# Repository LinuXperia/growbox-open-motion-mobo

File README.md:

# growbox-open-motion-mobo
A general purpose open source Arduino DUE based motion controller designed to run the Synthetos G2 motion control fimware 

Created and designed by Adam Vadala-Roth

https://hackaday.io/adamjvr

https://github.com/adamjvr

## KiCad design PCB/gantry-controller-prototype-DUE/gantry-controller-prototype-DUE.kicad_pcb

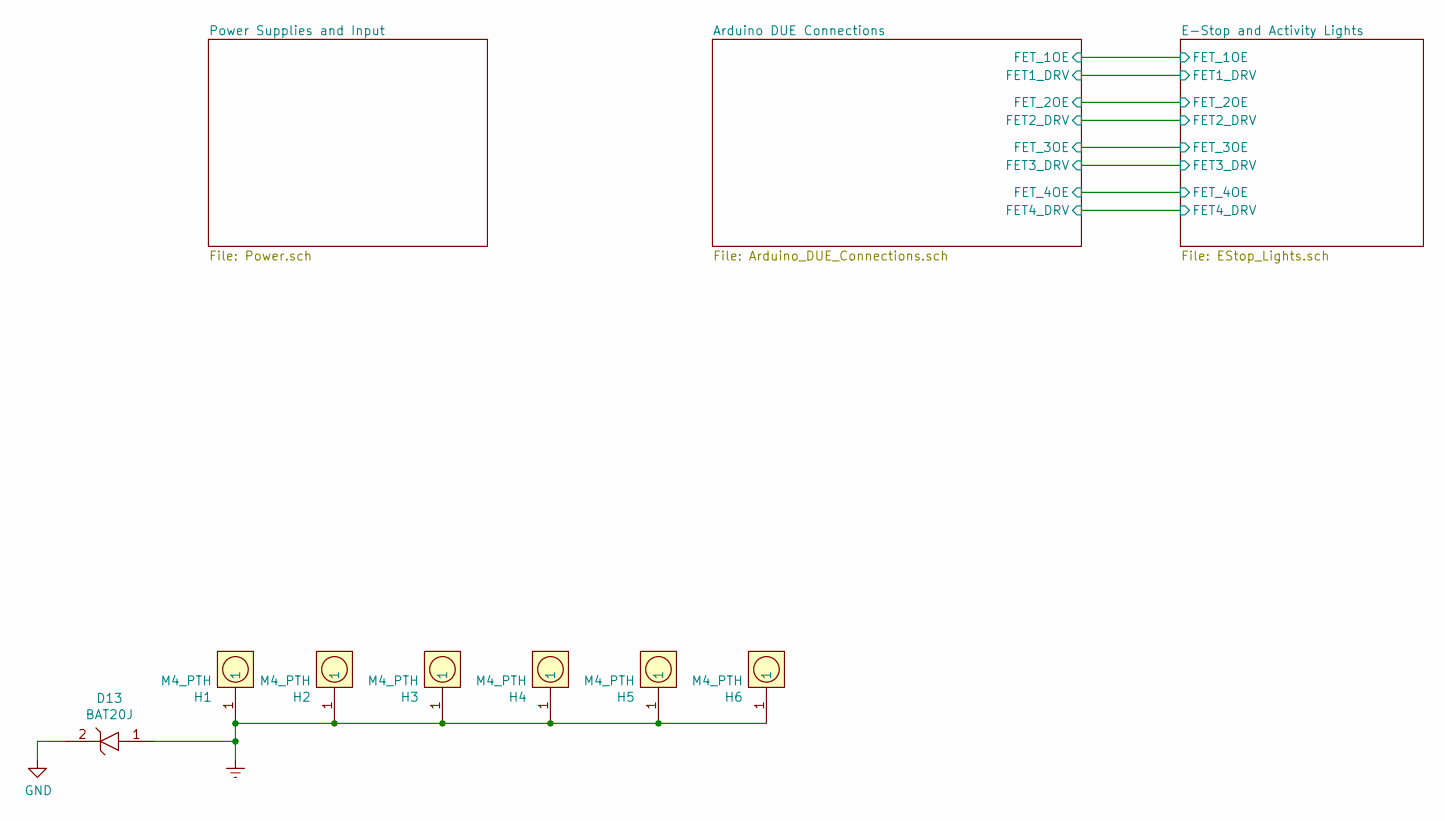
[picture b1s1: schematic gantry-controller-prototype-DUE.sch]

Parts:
D13: BAT20JFILM; Tolerance *; Voltage 23V; MFR# BAT20JFILM
H1, H2, H3, H4, H5, H6: M4_PTH; M4_HOLE; Tolerance *; Voltage *; MFR# *

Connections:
Earth: D13.1, H1.1, H2.1, H3.1, H4.1, H5.1, H6.1
GND: D13.2; also elsewhere on the board

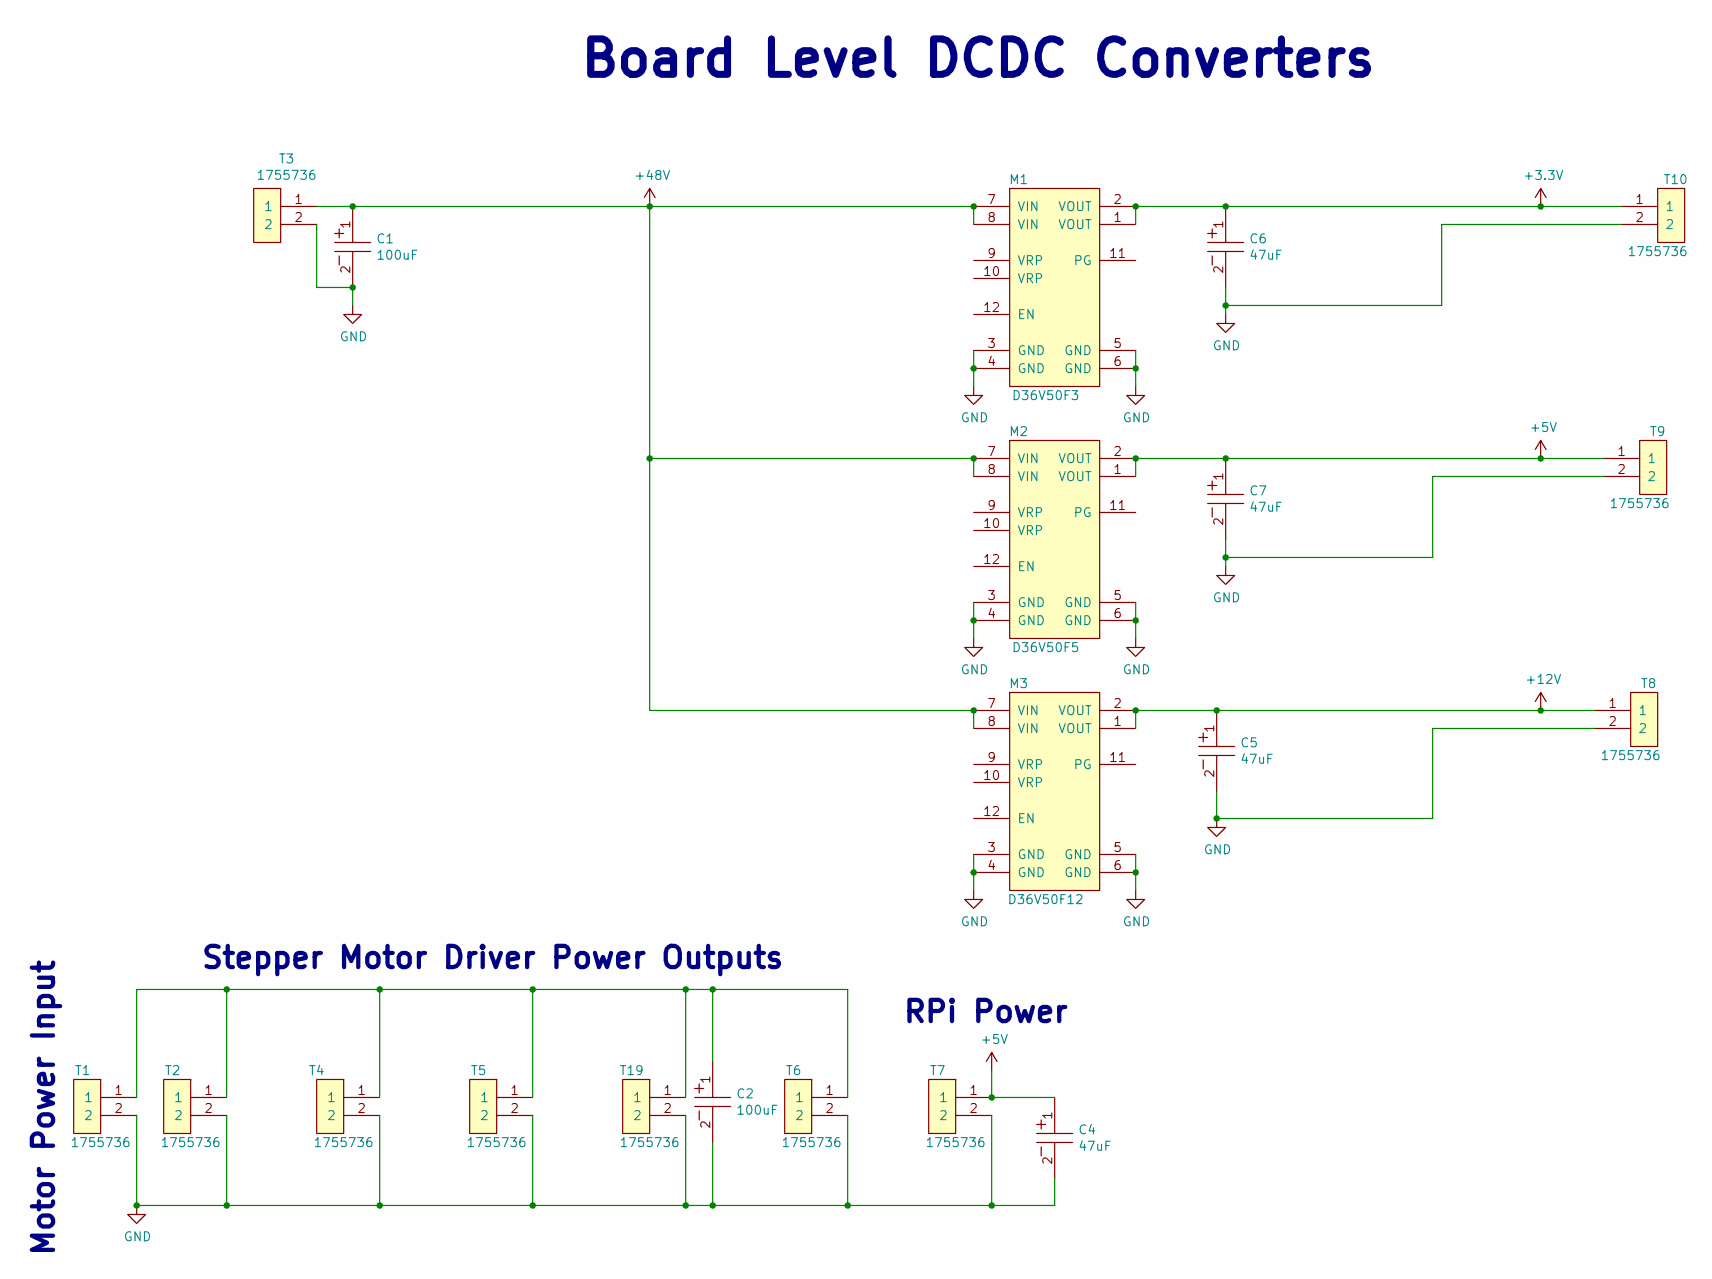
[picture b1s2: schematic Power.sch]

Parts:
C1, C2: UUX1J101MNL1GS; Tolerance 20%; Voltage 63V; MFR# UUX1J101MNL1GS
C4, C5, C6, C7: UWT1H470MCL1GS; Tolerance 20%; Voltage 63V; MFR# UWT1H470MCL1GS
M1: D36V50F3; D36V50Fx; Tolerance *; Voltage 50V In 3.3V OUT; MFR# D36V50F3
M2: D36V50F5; D36V50Fx; Tolerance *; Voltage 50V In 5V OUT; MFR# D36V50F5
M3: D36V50F12; D36V50Fx; Tolerance *; Voltage 50V In 12V OUT; MFR# D36V50F12
T1, T2, T3, T4, T5, T6, T7, T8, T9, T10, T19: 1755736; PhoenixContact_MSTBVA-G_02x5.08mm_Vertical; Tolerance *; Voltage 300V; MFR# 1755736

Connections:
+3V3: C6.1, M1.1 (VOUT), M1.2 (VOUT), T10.1; also elsewhere on the board
+5V: C4.1, C7.1, M2.1 (VOUT), M2.2 (VOUT), T7.1, T9.1; also elsewhere on the board
+12V: C5.1, M3.1 (VOUT), M3.2 (VOUT), T8.1; also elsewhere on the board
+48V: C1.1, M1.7 (VIN), M1.8 (VIN), M2.7 (VIN), M2.8 (VIN), M3.7 (VIN), M3.8 (VIN), T3.1
GND: C1.2, C2.2, C4.2, C5.2, C6.2, C7.2, M1.3 (GND), M1.4 (GND), M1.5 (GND), M1.6 (GND), M2.3 (GND), M2.4 (GND), M2.5 (GND), M2.6 (GND), M3.3 (GND), M3.4 (GND), M3.5 (GND), M3.6 (GND), T1.2, T2.2, T3.2, T4.2, T5.2, T6.2, T7.2, T8.2, T9.2, T10.2, T19.2; also elsewhere on the board
unnamed: C2.1, T1.1, T2.1, T4.1, T5.1, T6.1, T19.1

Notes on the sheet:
Board Level DCDC Converters
Stepper Motor Driver Power Outputs
RPi Power
Motor Power Input

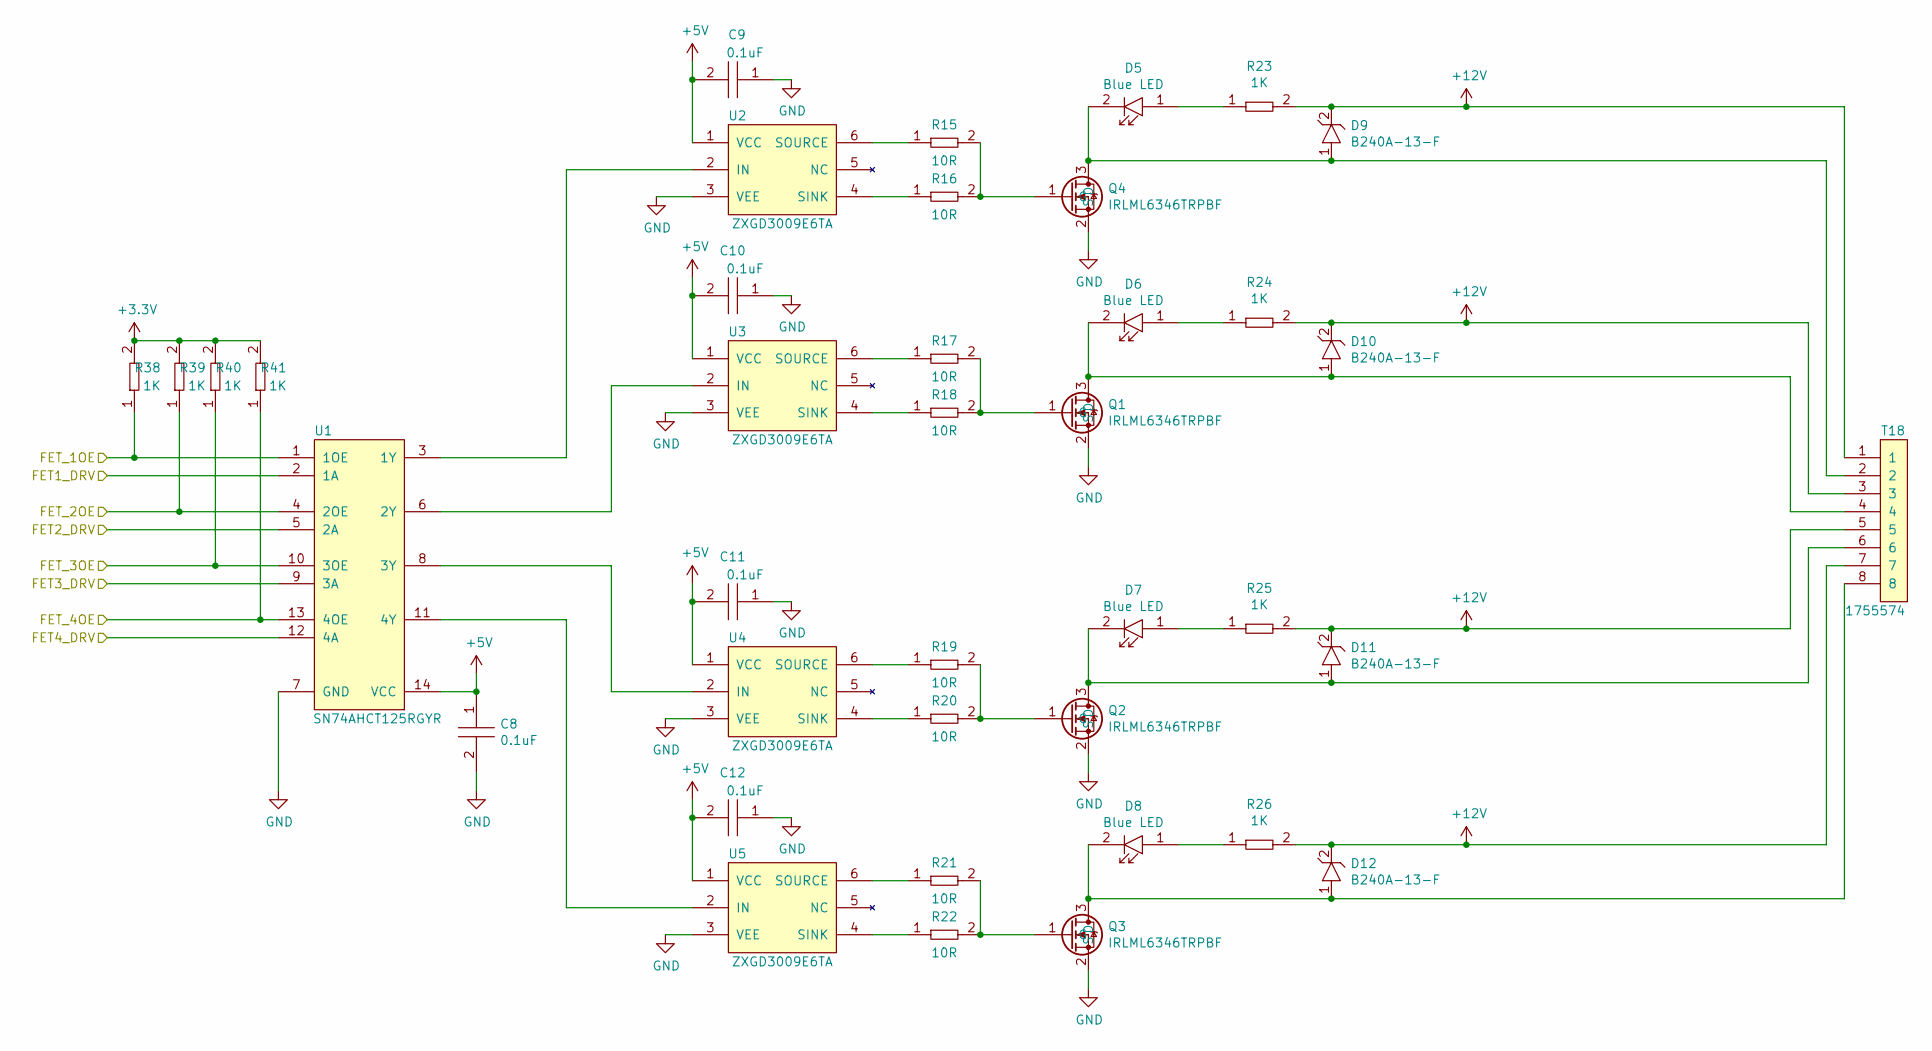
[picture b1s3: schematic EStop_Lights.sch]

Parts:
C8, C9, C10, C11, C12: GRM155R71E104KE14J; C0402; Tolerance 10%; Voltage 25V; MFR# GRM155R71E104KE14J
D5, D6, D7, D8: LTST-C194TBKT; LED0603; Tolerance *; Voltage 3.3V; MFR# LTST-C194TBKT
D9, D10, D11, D12: B240A-13-F; Tolerance *; Voltage 40V; MFR# B240A-13-F
Q1, Q2, Q3, Q4: IRLML6346TRPBF; SOT-23; Tolerance *; Voltage 30V; MFR# IRLML6346TRPBF
R15, R16, R17, R18, R19, R20, R21, R22: RC0402FR-0710RL; R0402; Tolerance 1%; Voltage *; MFR# RC0402FR-0710RL
R23, R24, R25, R26, R38, R39, R40, R41: RC0402FR-071KL; R0402; Tolerance 1%; Voltage *; MFR# RC0402FR-071KL
T18: 1755574; PhoenixContact_MSTBVA-G_08x5.00mm_Vertical; Tolerance *; Voltage 300V; MFR# 1755574
U1: SN74AHCT125RGYR; Tolerance *; Voltage 5V; MFR# SN74AHCT125RGYR
U2, U3, U4, U5: ZXGD3009E6TA; SOT-23-6_Handsoldering; Tolerance *; Voltage 40V; MFR# ZXGD3009E6TA

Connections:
+3V3: R38.2, R39.2, R40.2, R41.2; also elsewhere on the board
+5V: C8.1, C9.2, C10.2, C11.2, C12.2, U1.14 (VCC), U2.1 (VCC), U3.1 (VCC), U4.1 (VCC), U5.1 (VCC); also elsewhere on the board
+12V: D9.2, D10.2, D11.2, D12.2, R23.2, R24.2, R25.2, R26.2, T18.1, T18.3, T18.5, T18.7; also elsewhere on the board
/Arduino DUE Connections/FET1_DRV: U1.2 (1A); also elsewhere on the board
/Arduino DUE Connections/FET2_DRV: U1.5 (2A); also elsewhere on the board
/Arduino DUE Connections/FET3_DRV: U1.9 (3A); also elsewhere on the board
/Arduino DUE Connections/FET4_DRV: U1.12 (4A); also elsewhere on the board
/Arduino DUE Connections/FET_1OE: R38.1, U1.1 (1OE); also elsewhere on the board
/Arduino DUE Connections/FET_2OE: R39.1, U1.4 (2OE); also elsewhere on the board
/Arduino DUE Connections/FET_3OE: R40.1, U1.10 (3OE); also elsewhere on the board
/Arduino DUE Connections/FET_4OE: R41.1, U1.13 (4OE); also elsewhere on the board
GND: C8.2, C9.1, C10.1, C11.1, C12.1, Q1.2 (S), Q2.2 (S), Q3.2 (S), Q4.2 (S), U1.7 (GND), U2.3 (VEE), U3.3 (VEE), U4.3 (VEE), U5.3 (VEE); also elsewhere on the board
unnamed: D5.1, R23.1
unnamed: D5.2, D9.1, Q4.3 (D), T18.2
unnamed: D6.1, R24.1
unnamed: D7.1, R25.1
unnamed: D8.1, R26.1
unnamed: D6.2, D10.1, Q1.3 (D), T18.4
unnamed: D7.2, D11.1, Q2.3 (D), T18.6
unnamed: D8.2, D12.1, Q3.3 (D), T18.8
unnamed: Q1.1 (G), R17.2, R18.2
unnamed: Q2.1 (G), R19.2, R20.2
unnamed: Q3.1 (G), R21.2, R22.2
unnamed: Q4.1 (G), R15.2, R16.2
unnamed: R15.1, U2.6 (SOURCE)
unnamed: R16.1, U2.4 (SINK)
unnamed: R17.1, U3.6 (SOURCE)
unnamed: R18.1, U3.4 (SINK)
unnamed: R19.1, U4.6 (SOURCE)
unnamed: R20.1, U4.4 (SINK)
unnamed: R21.1, U5.6 (SOURCE)
unnamed: R22.1, U5.4 (SINK)
unnamed: U1.3 (1Y), U2.2 (IN)
unnamed: U1.6 (2Y), U3.2 (IN)
unnamed: U1.8 (3Y), U4.2 (IN)
unnamed: U1.11 (4Y), U5.2 (IN)

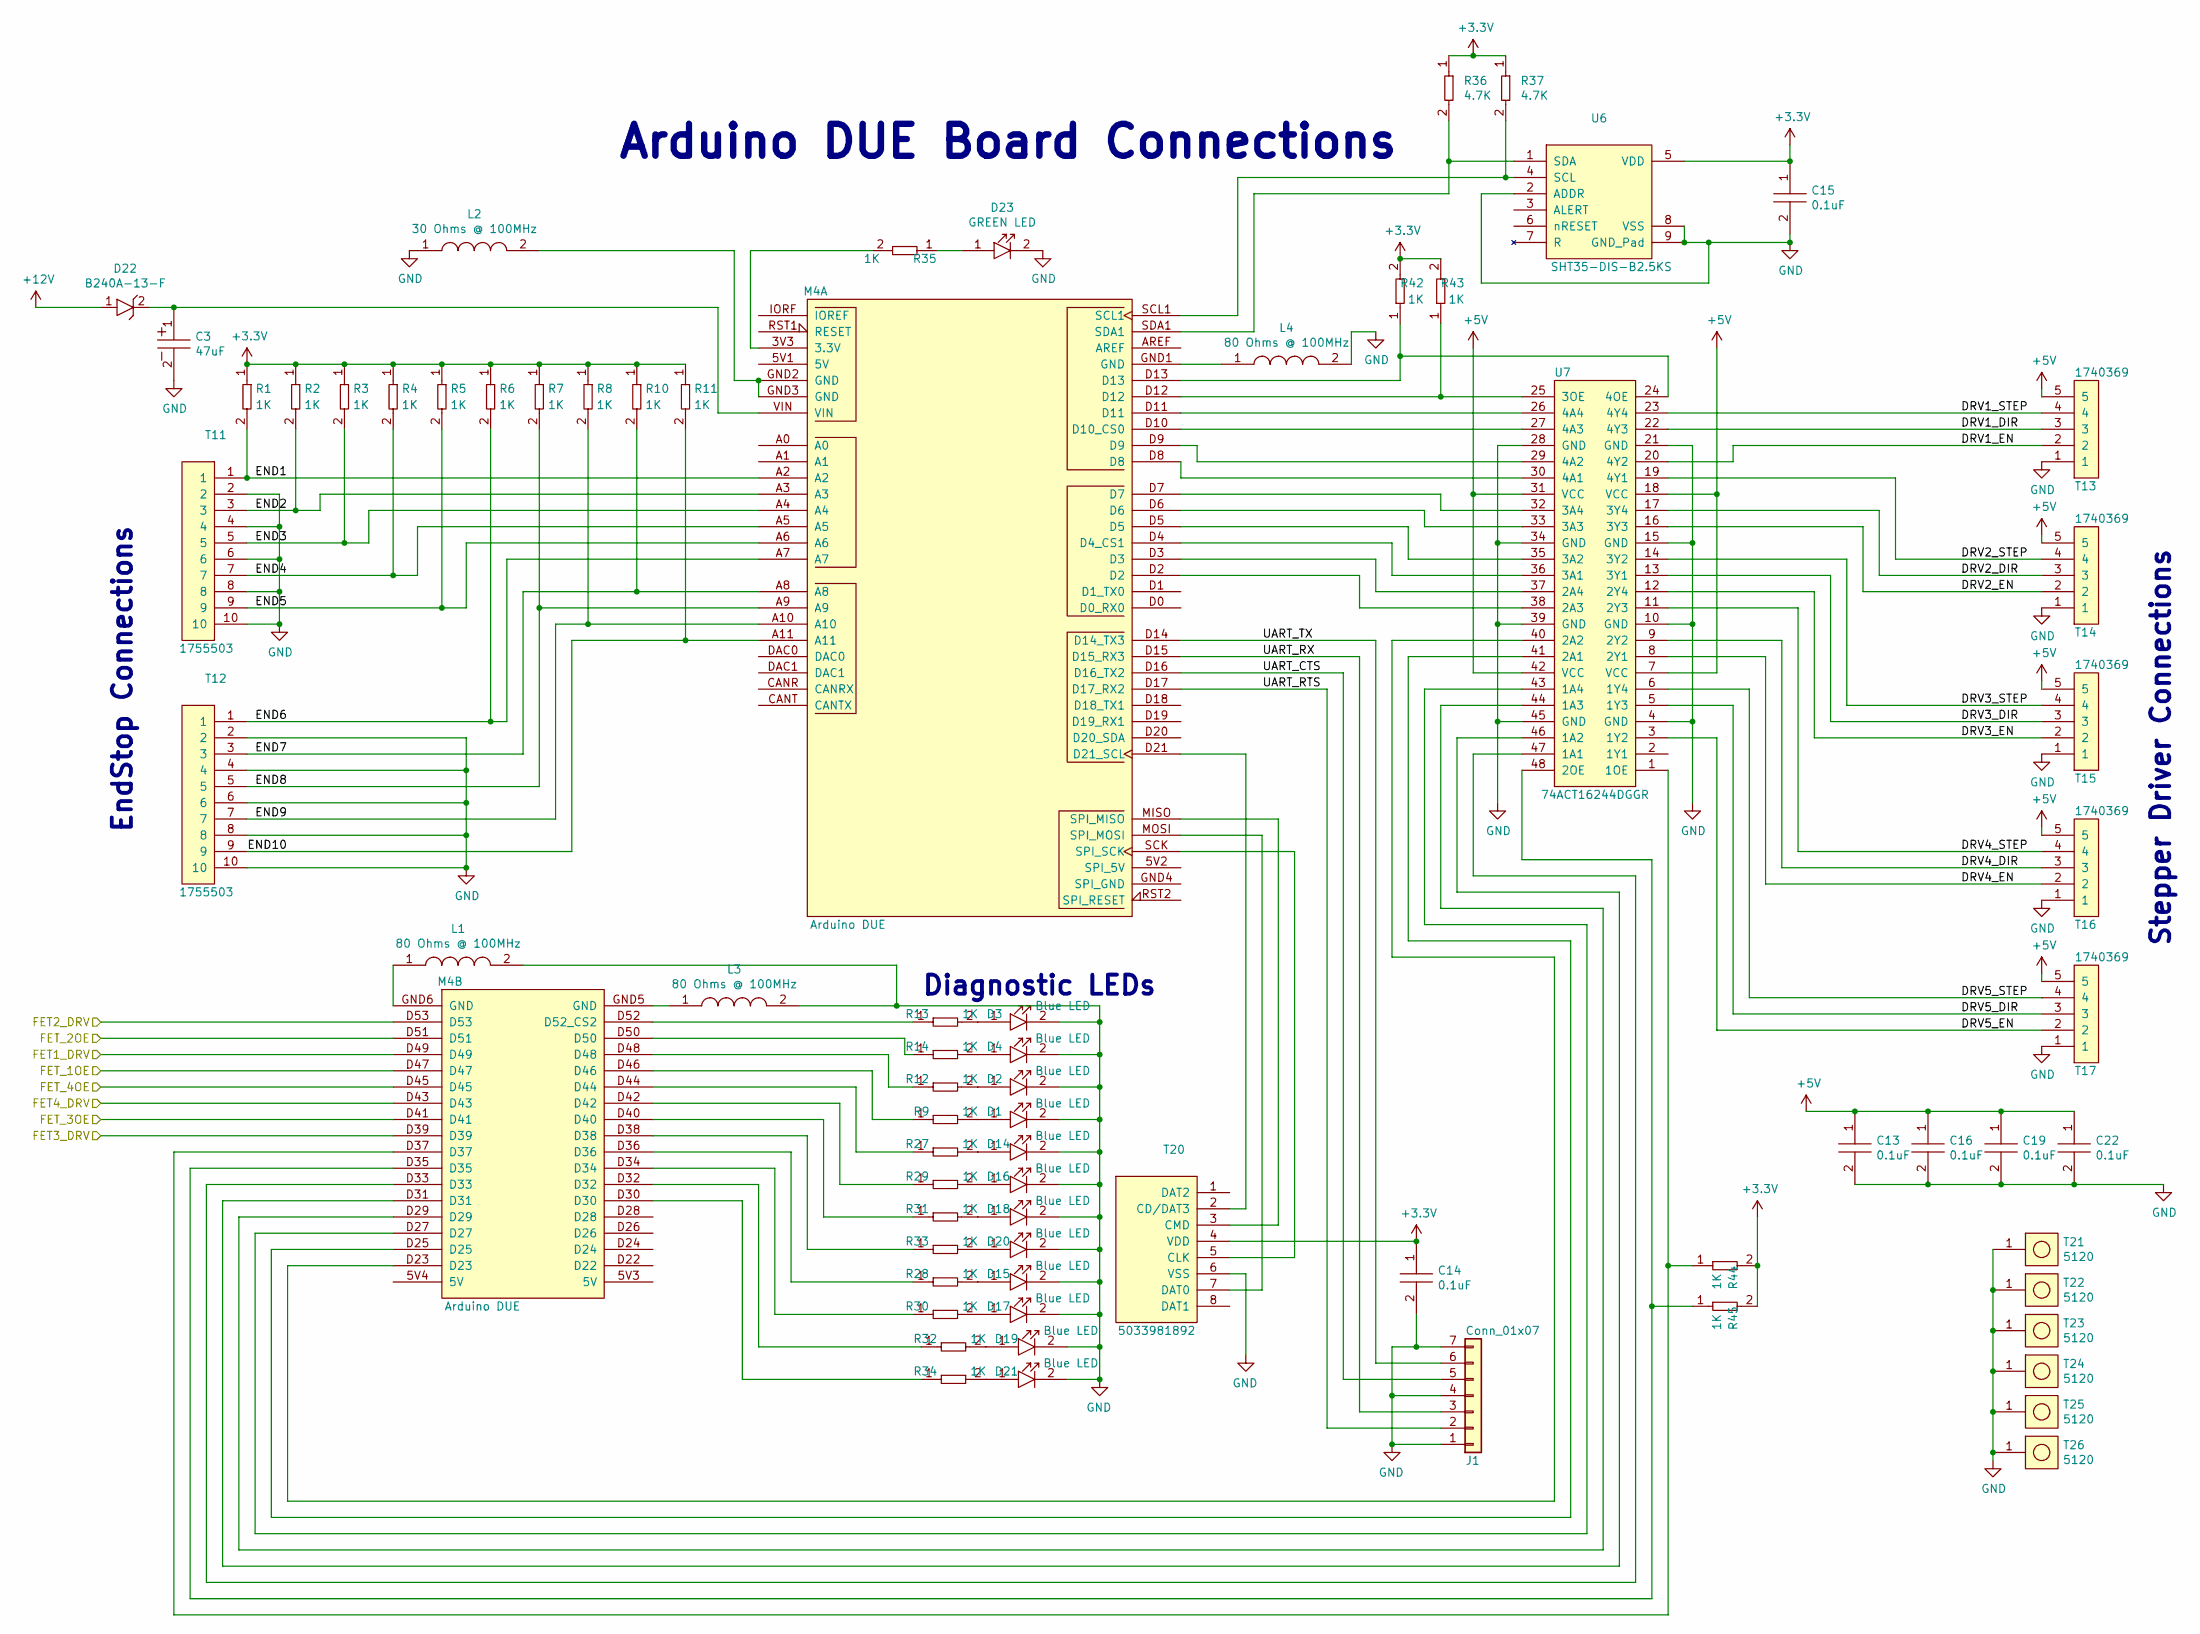
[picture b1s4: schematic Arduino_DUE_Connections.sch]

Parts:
C3: UWT1H470MCL1GS; Tolerance 20%; Voltage 63V; MFR# UWT1H470MCL1GS
C13, C14, C15, C16, C19, C22: GRM155R71E104KE14J; C0402; Tolerance 10%; Voltage 25V; MFR# GRM155R71E104KE14J
D1, D2, D3, D4, D14, D15, D16, D17, D18, D19, D20, D21: LTST-C194TBKT; LED0603; Tolerance *; Voltage 3.3V; MFR# LTST-C194TBKT
D22: B240A-13-F; Tolerance *; Voltage 40V; MFR# B240A-13-F
D23: LTST-C194KGKT; LED0603; Tolerance *; Voltage 2.1V; MFR# LTST-C194KGKT
J1: Conn_01x07; Pin_Header_Angled_1x07_Pitch2.54mm
L1, L3, L4: MH1608-800Y; I0603; Tolerance *; Voltage *; MFR# Bourns Inc.
L2: MH2029-300Y; Tolerance *; Voltage *; MFR# Bourns Inc.
M4: Arduino_DUE_Shield_TEMP; Arduino_Due_Shield; Tolerance *; Voltage *; MFR# *
R1, R2, R3, R4, R5, R6, R7, R8, R9, R10, R11, R12, R13, R14, R27, R28, R29, R30, R31, R32, R33, R34, R35, R42, R43, R44, R45: RC0402FR-071KL; R0402; Tolerance 1%; Voltage *; MFR# RC0402FR-071KL
R36, R37: RC0402FR-074K7L; R0402; Tolerance 1%; Voltage *; MFR# RC0402FR-074K7L
T11, T12: 1755503; PhoenixContact_MSTBVA-G_10x5.00mm_Vertical; Tolerance *; Voltage 300V; MFR# 1755503
T13, T14, T15, T16, T17: 1740369; PhoenixContact_MSTBVA-G_05x5.00mm_Vertical; Tolerance *; Voltage 300V; MFR# 1740369
T20: 5033981892; MOLEX_503398-1892; Tolerance *; Voltage 3.3V; MFR# 5033981892
T21, T22, T23, T24, T25, T26: 5120; Tolerance *; Voltage *; MFR# 5120
U6: SHT35-DIS-B2.5KS; DFN8_SHT35; Tolerance *; Voltage 2.15V-5.5V; MFR# SHT35-DIS-B2.5KS
U7: 74ACT16244DGGR; Tolerance *; Voltage 4.5V ~ 5.5V; MFR# 74ACT16244DGGR

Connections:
+3V3: C14.1, C15.1, R1.1, R2.1, R3.1, R4.1, R5.1, R6.1, R7.1, R8.1, R10.1, R11.1, R36.1, R37.1, R42.2, R43.2, R44.2, R45.2, T20.4 (VDD), U6.5 (VDD); also elsewhere on the board
+5V: C13.1, C16.1, C19.1, C22.1, T13.5, T14.5, T15.5, T16.5, T17.5, U7.7 (VCC), U7.18 (VCC), U7.31 (VCC), U7.42 (VCC); also elsewhere on the board
+12V: D22.1; also elsewhere on the board
/Arduino DUE Connections/DRV1_DIR: T13.3, U7.22 (4Y3)
/Arduino DUE Connections/DRV1_EN: T13.2, U7.20 (4Y2)
/Arduino DUE Connections/DRV1_STEP: T13.4, U7.23 (4Y4)
/Arduino DUE Connections/DRV2_DIR: T14.3, U7.17 (3Y4)
/Arduino DUE Connections/DRV2_EN: T14.2, U7.16 (3Y3)
/Arduino DUE Connections/DRV2_STEP: T14.4, U7.19 (4Y1)
/Arduino DUE Connections/DRV3_DIR: T15.3, U7.13 (3Y1)
/Arduino DUE Connections/DRV3_EN: T15.2, U7.12 (2Y4)
/Arduino DUE Connections/DRV3_STEP: T15.4, U7.14 (3Y2)
/Arduino DUE Connections/DRV4_DIR: T16.3, U7.9 (2Y2)
/Arduino DUE Connections/DRV4_EN: T16.2, U7.8 (2Y1)
/Arduino DUE Connections/DRV4_STEP: T16.4, U7.11 (2Y3)
/Arduino DUE Connections/DRV5_DIR: T17.3, U7.5 (1Y3)
/Arduino DUE Connections/DRV5_EN: T17.2, U7.3 (1Y2)
/Arduino DUE Connections/DRV5_STEP: T17.4, U7.6 (1Y4)
/Arduino DUE Connections/END1: M4.A2, R1.2, T11.1
/Arduino DUE Connections/END2: M4.A3, R2.2, T11.3
/Arduino DUE Connections/END3: M4.A4, R3.2, T11.5
/Arduino DUE Connections/END4: M4.A5, R4.2, T11.7
/Arduino DUE Connections/END5: M4.A6, R5.2, T11.9
/Arduino DUE Connections/END6: M4.A7, R6.2, T12.1
/Arduino DUE Connections/END7: M4.A8, R10.2, T12.3
/Arduino DUE Connections/END8: M4.A9, R7.2, T12.5
/Arduino DUE Connections/END9: M4.A10, R8.2, T12.7
/Arduino DUE Connections/END10: M4.A11, R11.2, T12.9
/Arduino DUE Connections/FET1_DRV: M4.D49; also elsewhere on the board
/Arduino DUE Connections/FET2_DRV: M4.D53; also elsewhere on the board
/Arduino DUE Connections/FET3_DRV: M4.D39; also elsewhere on the board
/Arduino DUE Connections/FET4_DRV: M4.D43; also elsewhere on the board
/Arduino DUE Connections/FET_1OE: M4.D47; also elsewhere on the board
/Arduino DUE Connections/FET_2OE: M4.D51; also elsewhere on the board
/Arduino DUE Connections/FET_3OE: M4.D41; also elsewhere on the board
/Arduino DUE Connections/FET_4OE: M4.D45; also elsewhere on the board
/Arduino DUE Connections/UART_CTS: J1.5, M4.D16 (D16_TX2)
/Arduino DUE Connections/UART_RTS: J1.2, M4.D17 (D17_RX2)
/Arduino DUE Connections/UART_RX: J1.3, M4.D15 (D15_RX3)
/Arduino DUE Connections/UART_TX: J1.6, M4.D14 (D14_TX3)
GND: C3.2, C13.2, C14.2, C15.2, C16.2, C19.2, C22.2, D1.2, D2.2, D3.2, D4.2, D14.2, D15.2, D16.2, D17.2, D18.2, D19.2, D20.2, D21.2, D23.2, J1.1, J1.4, J1.7, L1.2, L2.1, L3.2, L4.2, T11.2, T11.4, T11.6, T11.8, T11.10, T12.2, T12.4, T12.6, T12.8, T12.10, T13.1, T14.1, T15.1, T16.1, T17.1, T20.6 (VSS), T21.1, T22.1, T23.1, T24.1, T25.1, T26.1, U6.2 (ADDR), U6.8 (VSS), U6.9 (GND_Pad), U7.4 (GND), U7.10 (GND), U7.15 (GND), U7.21 (GND), U7.28 (GND), U7.34 (GND), U7.39 (GND), U7.45 (GND); also elsewhere on the board
unnamed: C3.1, D22.2, M4.VIN
unnamed: D1.1, R9.2
unnamed: D2.1, R12.2
unnamed: D3.1, R13.2
unnamed: D4.1, R14.2
unnamed: D14.1, R27.2
unnamed: D15.1, R28.2
unnamed: D16.1, R29.2
unnamed: D17.1, R30.2
unnamed: D18.1, R31.2
unnamed: D19.1, R32.2
unnamed: D20.1, R33.2
unnamed: D21.1, R34.2
unnamed: D23.1, R35.1
unnamed: L1.1, M4.GND6 (GND)
unnamed: L2.2, M4.GND2 (GND), M4.GND3 (GND)
unnamed: L3.1, M4.GND5 (GND)
unnamed: L4.1, M4.GND1 (GND)
unnamed: M4.3V3 (3.3V), R35.2
unnamed: M4.D2, U7.38 (2A3)
unnamed: M4.D3, U7.37 (2A4)
unnamed: M4.D4 (D4_CS1), U7.36 (3A1)
unnamed: M4.D5, U7.35 (3A2)
unnamed: M4.D6, U7.33 (3A3)
unnamed: M4.D7, U7.32 (3A4)
unnamed: M4.D8, U7.30 (4A1)
unnamed: M4.D9, U7.29 (4A2)
unnamed: M4.D10 (D10_CS0), U7.27 (4A3)
unnamed: M4.D11, U7.26 (4A4)
unnamed: M4.D12, R43.1, U7.25 (3OE)
unnamed: M4.D13, R42.1, U7.24 (4OE)
unnamed: M4.D21 (D21_SCL), T20.2 (CD/DAT3)
unnamed: M4.D23, U7.40 (2A2)
unnamed: M4.D25, U7.41 (2A1)
unnamed: M4.D27, U7.43 (1A4)
unnamed: M4.D29, U7.44 (1A3)
unnamed: M4.D30, R34.1
unnamed: M4.D31, U7.46 (1A2)
unnamed: M4.D32, R32.1
unnamed: M4.D33, U7.47 (1A1)
unnamed: M4.D34, R30.1
unnamed: M4.D35, R45.1, U7.48 (2OE)
unnamed: M4.D36, R28.1
unnamed: M4.D37, R44.1, U7.1 (1OE)
unnamed: M4.D38, R33.1
unnamed: M4.D40, R31.1
unnamed: M4.D42, R29.1
unnamed: M4.D44, R27.1
unnamed: M4.D46, R9.1
unnamed: M4.D48, R12.1
unnamed: M4.D50, R14.1
unnamed: M4.D52 (D52_CS2), R13.1
unnamed: M4.MISO (SPI_MISO), T20.3 (CMD)
unnamed: M4.MOSI (SPI_MOSI), T20.7 (DAT0)
unnamed: M4.SCK (SPI_SCK), T20.5 (CLK)
unnamed: M4.SCL1, R37.2, U6.4 (SCL)
unnamed: M4.SDA1, R36.2, U6.1 (SDA)

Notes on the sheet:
Arduino DUE Board Connections
EndStop Connections
Diagnostic LEDs
Stepper Driver Connections

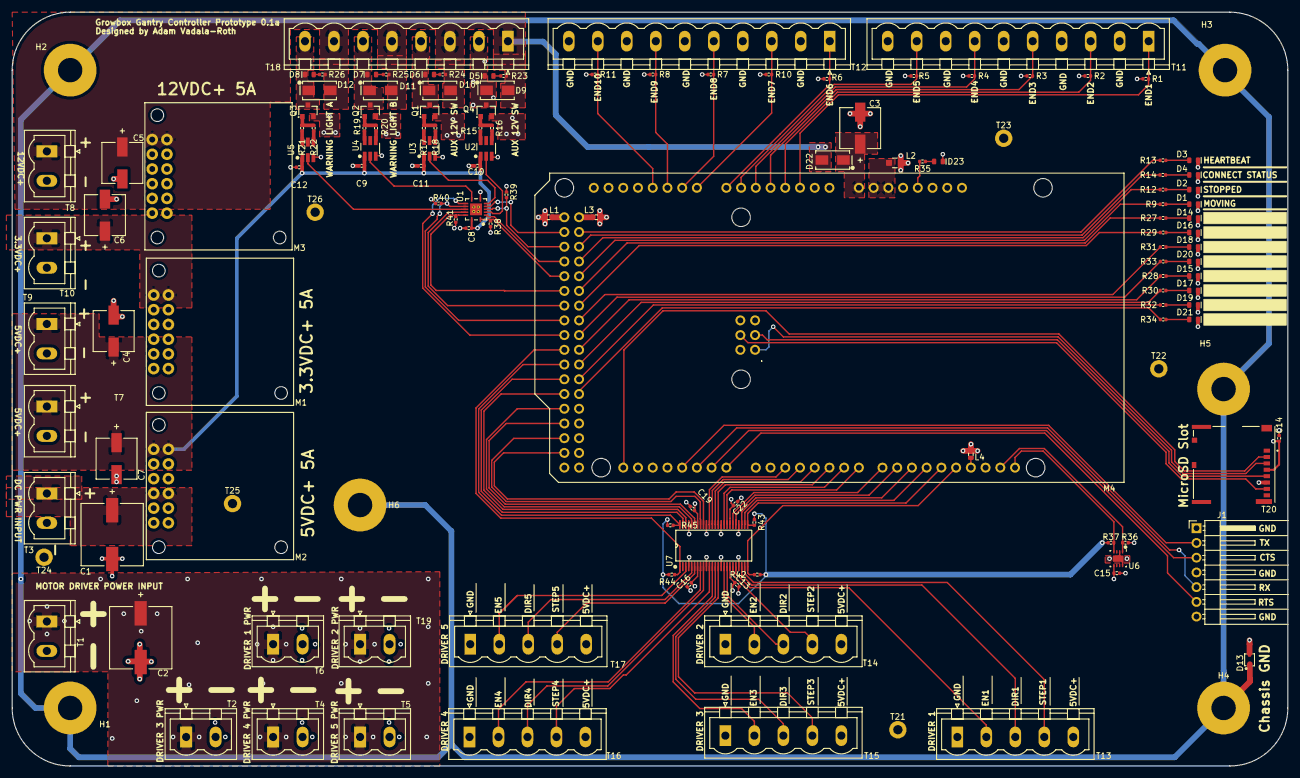
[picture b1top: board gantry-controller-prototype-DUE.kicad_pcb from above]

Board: 4 copper layers, 220.0 x 130.0 mm, 138 parts (0 on the bottom side), 125 nets.

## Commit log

2020-06-16 Release
    Open Source release of internal development motion control hardware.
2020-06-17 Fab files and edits
    made some changes to the circuit, added pullups to OE pins on 74 devices and tied mosfet drivers to GND, added fab files
2020-06-17 DRC check and gerbers generated, order placed with OSHPark
2020-06-18 Renders
    3D rendered images added

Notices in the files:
parts and their libraries:
Copyright 2016 Accelerated Designs. All rights reserved.
